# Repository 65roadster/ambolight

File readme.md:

# Ray's Retirement Nest Egg Calculator

<br />

## Overview
Drew bought an old ambulance to fix up into an RV. I wanted to contribute so I created an ESP32 controlled light.

The light has a ring of around 80- addressable RGBW LEDs.

The board accomodates 12V to 5V @ 3A switching supply to drive the LEDs using the TPS54331DDAR.

The ESP32 is programmed with WLED. 10 of these are controlled by Home Assistant.

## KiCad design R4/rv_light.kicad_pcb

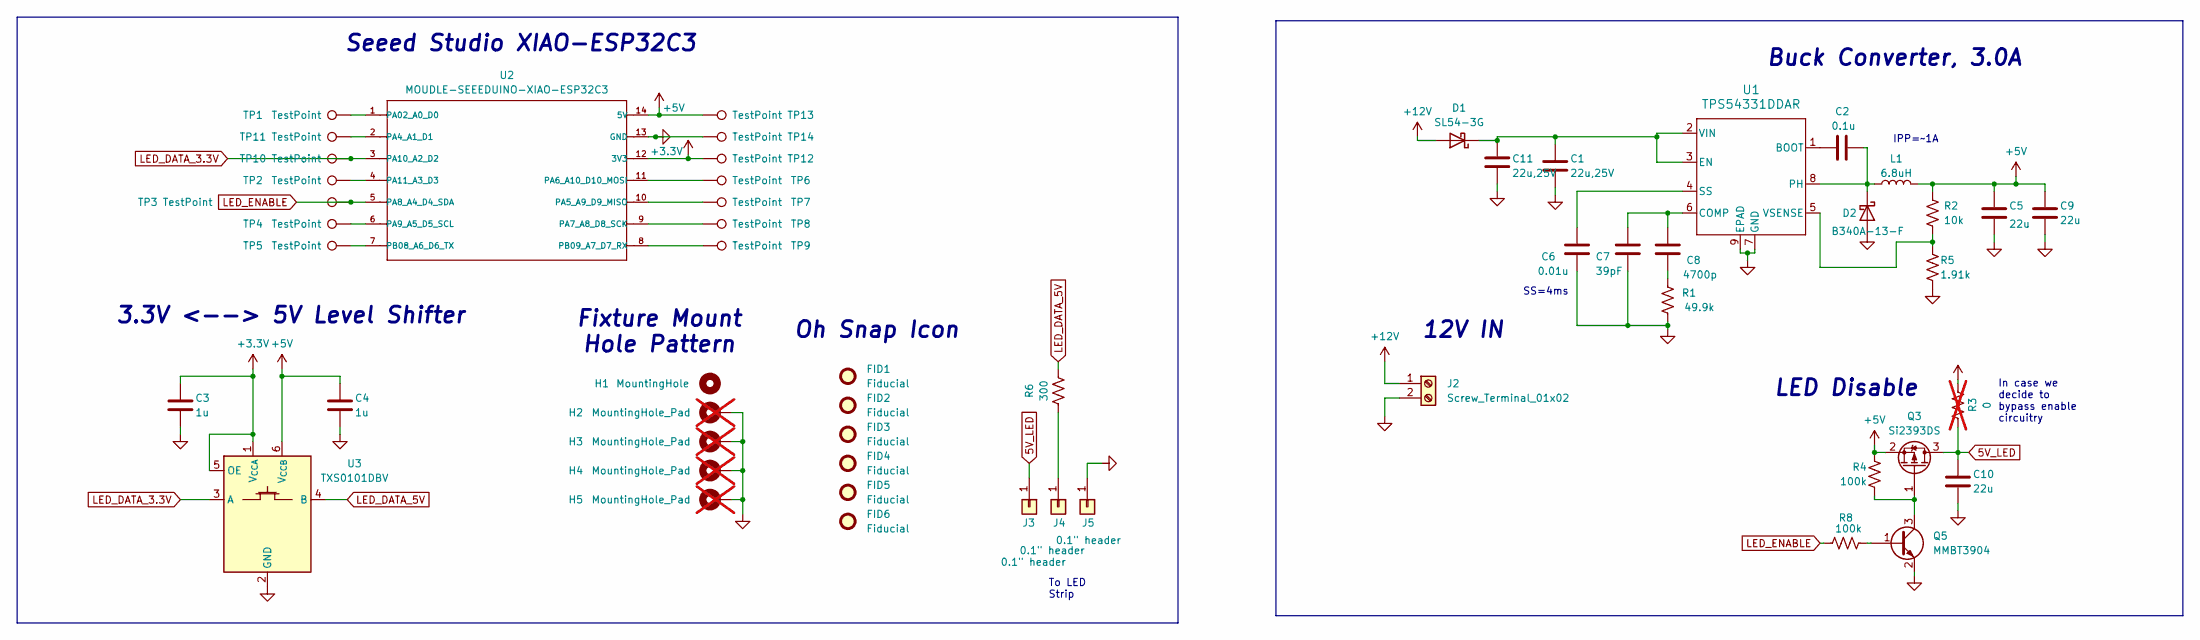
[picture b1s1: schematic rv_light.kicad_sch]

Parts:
C1, C11: 22u,25V; C_0805_2012Metric_Pad1.18x1.45mm_HandSolder
C2: 0.1u; C_0603_1608Metric_Pad1.08x0.95mm_HandSolder
C3, C4: 1u; C_0603_1608Metric_Pad1.08x0.95mm_HandSolder
C5, C9, C10: 22u; C_0805_2012Metric_Pad1.18x1.45mm_HandSolder
C6: 0.01u; C_0603_1608Metric_Pad1.08x0.95mm_HandSolder
C7: 39pF; C_0603_1608Metric_Pad1.08x0.95mm_HandSolder
C8: 4700p; C_0603_1608Metric_Pad1.08x0.95mm_HandSolder
D1: SL54-3G; D_SMB_Handsoldering
D2: B340A-13-F; D_SMA_Handsoldering
FID1, FID2, FID3, FID4, FID5, FID6: Fiducial; brokedit_icon_750x750
H1: MountingHole; Mount-Hole-#4-NoPad
H2, H3, H4, H5: MountingHole_Pad; Mount-Hole-#4; not fitted
J2: Screw_Terminal_01x02; CONN_OSTVN02A150_OST
J3, J4, J5: 0.1" header; PinHeader_1x01_P2.54mm_Vertical
L1: 6.8uH; L_Bourns_SRN8040TA
Q3: Si2393DS; TSOT-23
Q5: MMBT3904; SOT-23
R1: 49.9k; R_0603_1608Metric_Pad0.98x0.95mm_HandSolder
R2: 10k; R_0603_1608Metric_Pad0.98x0.95mm_HandSolder
R3: 0; R_0603_1608Metric_Pad0.98x0.95mm_HandSolder; not fitted
R4, R8: 100k; R_0603_1608Metric_Pad0.98x0.95mm_HandSolder
R5: 1.91k; R_0603_1608Metric_Pad0.98x0.95mm_HandSolder
R6: 300; R_0603_1608Metric_Pad0.98x0.95mm_HandSolder
TP1, TP2, TP3, TP4, TP5, TP6, TP7, TP8, TP9, TP10, TP11, TP12, TP13, TP14: TestPoint; TP_Wire-26ga
U1: TPS54331DDAR; DDA8_3X2P13-M
U2: MOUDLE-SEEEDUINO-XIAO-ESP32C3; SeeedStudio-MOUDLE14P-SMD-2.54-21X17.8MM
U3: TXS0101DBV; SOT-23-6

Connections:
5V_LED: C10.1, J3.1, Q3.3 (D), R3.1
+3.3V: C3.1, TP12.1, U2.12 (3V3), U3.1 (V_{CCA}), U3.5 (OE)
+5V: C4.1, C5.1, C9.1, L1.2, Q3.2 (S), R2.1, R3.2, R4.1, TP13.1, U2.14 (5V), U3.6 (V_{CCB})
+12V: D1.2 (A), J2.1
GND: C1.2, C3.2, C4.2, C5.2, C6.2, C7.2, C9.2, C10.2, C11.2, D2.2 (A), H2.1, H3.1, H4.1, H5.1, J2.2, J5.1, Q5.2 (E), R1.2, R5.2, TP14.1, U1.7 (GND), U1.9 (EPAD), U2.13 (GND), U3.2 (GND)
LED_DATA_3.3V: TP10.1, U2.3 (PA10_A2_D2), U3.3 (A)
LED_DATA_5V: R6.1, U3.4 (B)
LED_ENABLE: R8.1, TP3.1, U2.5 (PA8_A4_D4_SDA)
unnamed: C8.2, R1.1
unnamed: C1.1, C11.1, D1.1 (K), U1.2 (VIN), U1.3 (EN)
unnamed: C2.1, D2.1 (K), L1.1, U1.8 (PH)
unnamed: J4.1, R6.2
unnamed: Q3.1 (G), Q5.3 (C), R4.2
unnamed: Q5.1 (B), R8.2
unnamed: C2.2, U1.1 (BOOT)
unnamed: C7.1, C8.1, U1.6 (COMP)
unnamed: C6.1, U1.4 (SS)
unnamed: R2.2, R5.1, U1.5 (VSENSE)
unnamed: TP1.1, U2.1 (PA02_A0_D0)
unnamed: TP11.1, U2.2 (PA4_A1_D1)
unnamed: TP7.1, U2.10 (PA5_A9_D9_MISO)
unnamed: TP6.1, U2.11 (PA6_A10_D10_MOSI)
unnamed: TP8.1, U2.9 (PA7_A8_D8_SCK)
unnamed: TP4.1, U2.6 (PA9_A5_D5_SCL)
unnamed: TP2.1, U2.4 (PA11_A3_D3)
unnamed: TP5.1, U2.7 (PB08_A6_D6_TX)
unnamed: TP9.1, U2.8 (PB09_A7_D7_RX)

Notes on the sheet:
IPP=~1A
LED Disable
Buck Converter, 3.0A
Oh Snap Icon
In case we decide to bypass enable circuitry
12V IN
Seeed Studio XIAO-ESP32C3
SS=4ms
Fixture Mount Hole Pattern
To LED Strip
3.3V <--> 5V Level Shifter

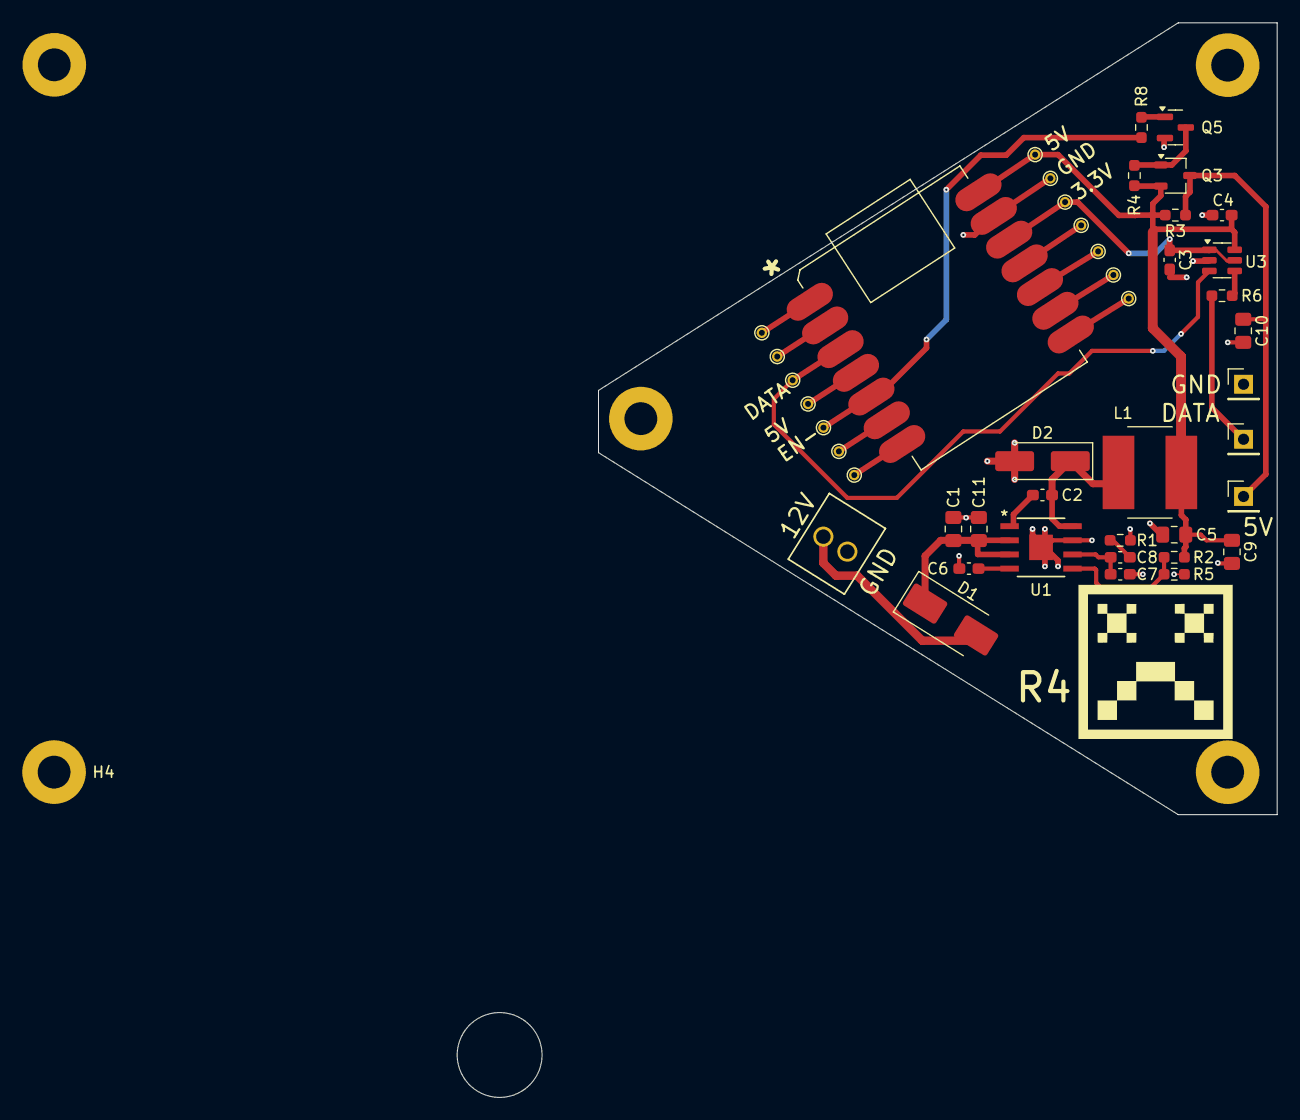
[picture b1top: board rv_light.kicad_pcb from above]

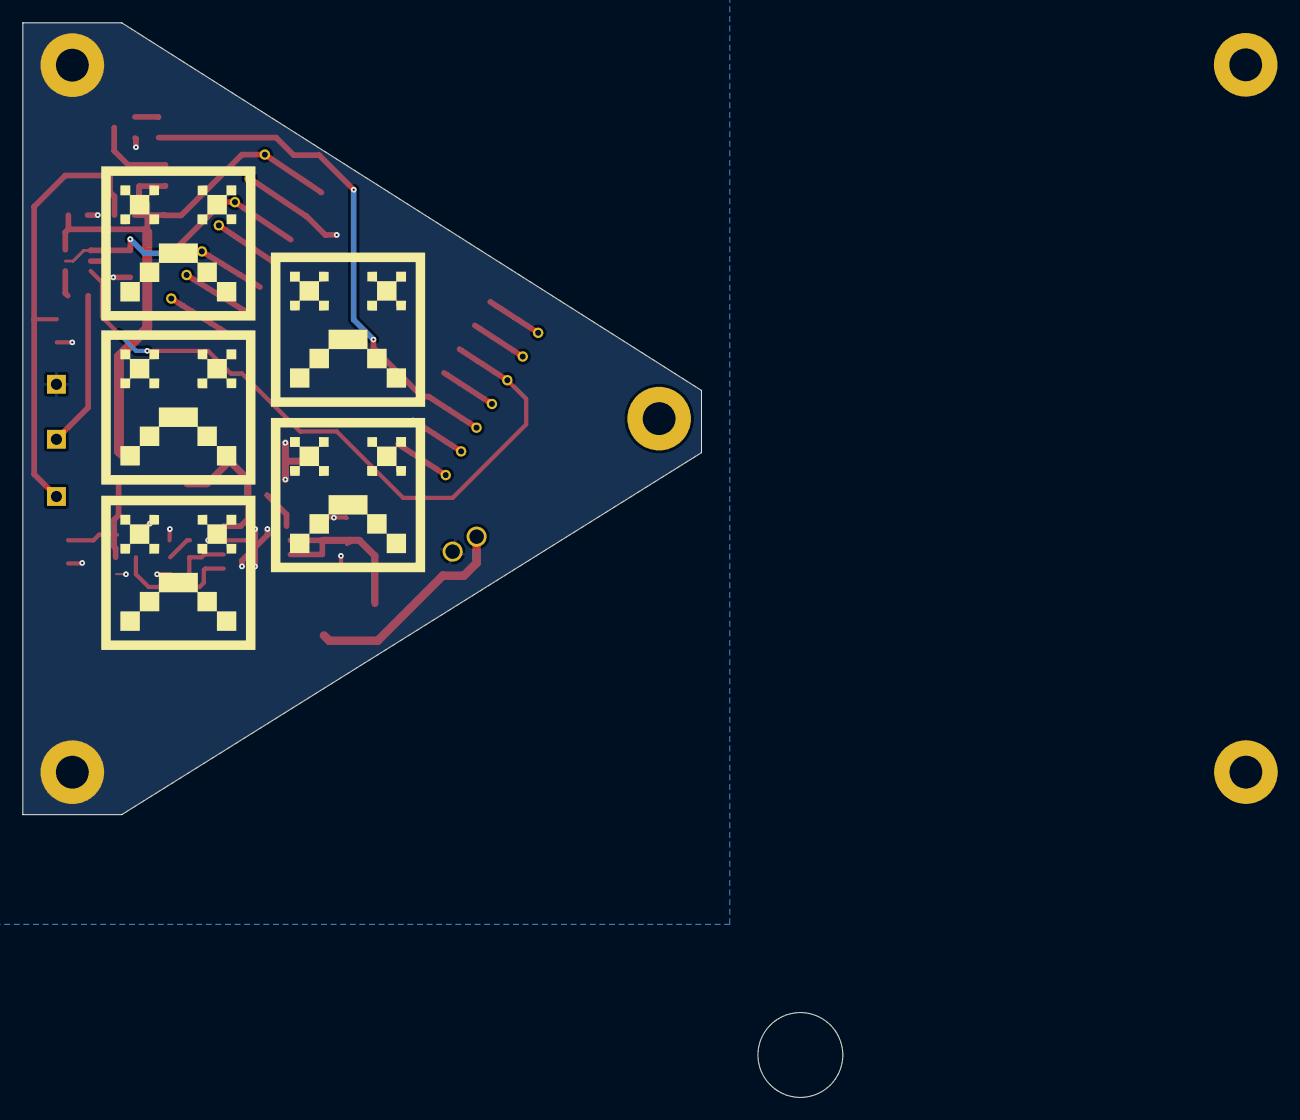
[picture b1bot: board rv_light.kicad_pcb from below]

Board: 2 copper layers, 61.0 x 71.1 mm, 55 parts (5 on the bottom side), 27 nets.

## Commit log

2026-01-20 r4 release
